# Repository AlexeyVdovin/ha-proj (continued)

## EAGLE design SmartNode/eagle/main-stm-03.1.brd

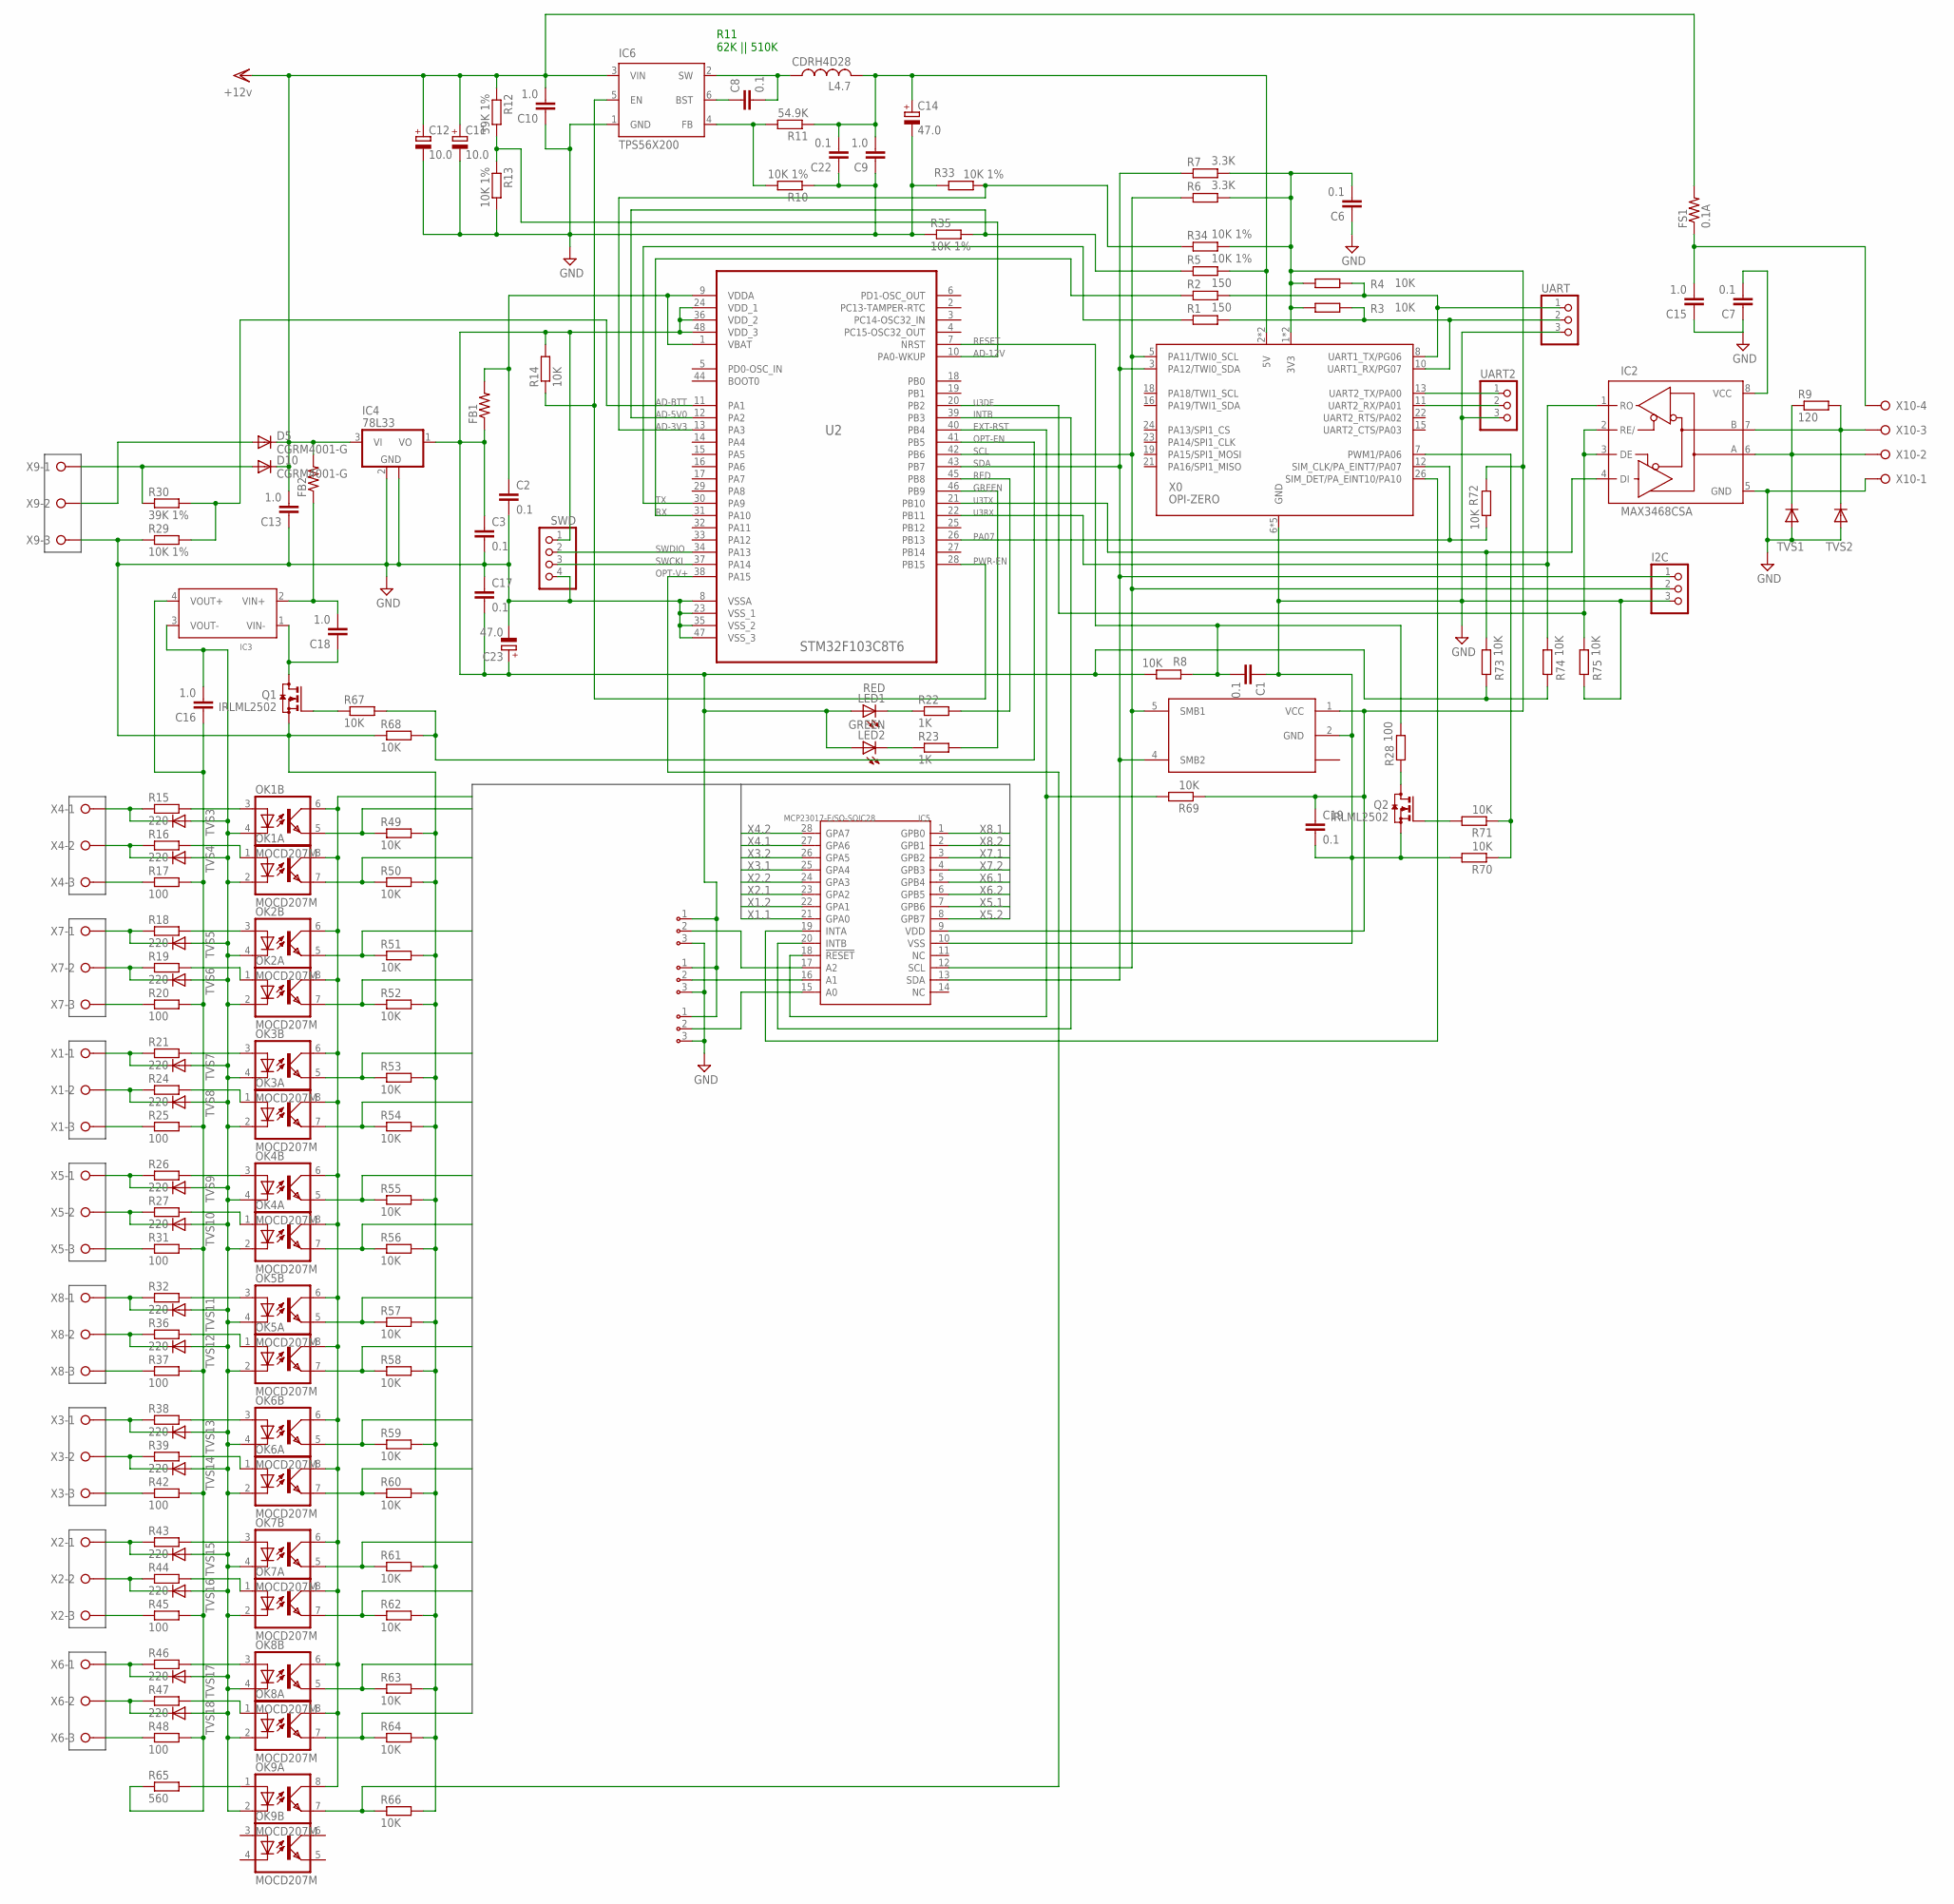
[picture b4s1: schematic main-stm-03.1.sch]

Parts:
A0, A1, A2: ADDR3PIN0603; 0603-3PIN
C1, C2, C3, C17, C19: 0.1; C0603
C6, C7, C8, C22: 0.1; C0805
C9: 1.0; C0805
C10, C13, C15, C16, C18: 1.0; C1206
C11, C12: 10.0; C/6032-28R
C14, C23: 47.0; B/3528-21R
D5, D10: CGRM4001-G; SOD-123_MINI-SMA
FB1: R-US_R0805; R0805
FB2: R-US_R1206; R1206
FS1: 0.1A; R1210
I2C: PINHD-1X3; 1X03
IC2: MAX3468CSA; SO08
IC3: DC-DC-CONV-4PIN-ISOLATINGMURATA-NME-05-12-SERIES; DC-DC-MURATA-NME-05-12-SERIES
IC4: 78L33; SOT89
IC5: MCP23017-E/SO-SOIC28; SOIC28-1.27-17.9X7.5MM
IC6: TPS56X200; TSOT23-6_DDC
IC7: LTC1694; SOT23-5
L4.7: CDRH4D28
LED1: RED; CHIPLED_1206
LED2: GREEN; CHIPLED_1206
OK1, OK2, OK3, OK4, OK5, OK6, OK7, OK8, OK9: MOCD207M; SOIC08-FAIRCHILD
Q1, Q2: IRLML2502; SOT23
R1, R2: 150; R0603
R3, R4, R8, R14, R49, R50, R51, R52, R53, R54, R55, R56, R57, R58, R59, R60, R61, R62, R63, R64, R66, R67, R68, R69, R70, R71, R72, R73, R74, R75: 10K; R0603
R5, R10, R13, R29, R33, R34, R35: 10K 1%; R0603
R6, R7: 3.3K; R0603
R9: 120; R1206
R11: 54.9K; R0603
R12, R30: 39K 1%; R0603
R15, R16, R18, R19, R21, R24, R26, R27, R32, R36, R38, R39, R43, R44, R46, R47: 220; R0603
R17, R20, R25, R28, R31, R37, R42, R45, R48: 100; R0603
R22, R23: 1K; R0603
R65: 560; R0603
SWD: PINHD-1X4; 1X04
TVS1, TVS2, TVS3, TVS4, TVS5, TVS6, TVS7, TVS8, TVS9, TVS10, TVS11, TVS12, TVS13, TVS14, TVS15, TVS16, TVS17, TVS18: DIODE-SOD323-W; SOD323-W
U2: STM32F103C8T6; QFP50P900X900X160-48N
UART, UART2: PINHD-1X3; 1X03
X0: OPI-ZERO; OPI0
X1, X2, X3, X4, X5, X6, X7, X8, X9: W237-03P; W237-133
X10: W237-04P; W237-4P

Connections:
12V: C10.2, C11.+, C12.+, C13.2, D5.C, D10.C, FB2.2, FS1.2, IC4.3 (VI), IC6.3 (VIN), R12.1
AD-3V3: R33.1, R34.1, U2.13 (PA3)
AD-5V0: R5.1, R35.2, U2.12 (PA2)
AD-12V: R12.2, R13.1, U2.10 (PA0-WKUP)
AD-BTT: R29.2, R30.2, U2.11 (PA1)
EXT-RST: IC5.18 (!RESET), R69.2, U2.40 (PB4)
GND: A0.3, A1.3, A2.3, C1.1, C2.2, C3.2, C6.1, C7.1, C9.1, C10.1, C11.-, C12.-, C13.1, C14.-, C15.1, C17.1, C19.2, C22.1, C23.-, I2C.3, IC2.5 (GND), IC4.2 (GND), IC4.2@1 (GND), IC5.10 (VSS), IC6.1 (GND), IC7.2 (GND), Q1.2 (S), Q2.2 (S), R10.1, R13.2, R29.1, R33.2, R35.1, R49.2, R50.2, R51.2, R52.2, R53.2, R54.2, R55.2, R56.2, R57.2, R58.2, R59.2, R60.2, R61.2, R62.2, R63.2, R64.2, R66.2, R68.1, R70.2, R75.1, SWD.4, TVS1.A, TVS2.A, U2.8 (VSSA), U2.23 (VSS_1), U2.35 (VSS_2), U2.47 (VSS_3), UART.3, UART2.3, X0.6 (GND), X0.9 (GND), X0.14 (GND), X0.20 (GND), X0.25 (GND), X9.3, X10.1
GREEN: R23.2, U2.46 (PB9)
INTA: IC5.19 (INTA), X0.26 (SIM_DET/PA_EINT10/PA10)
INTB: IC5.20 (INTB), U2.39 (PB3)
unnamed: C8.2, IC6.2 (SW), L4.7.P$1 (1)
unnamed: Q2.3 (D), R28.1
unnamed: Q2.1 (G), R71.2
unnamed: D5.A, X9.2
unnamed: OK1.3 (A), R15.2
unnamed: C8.1, IC6.6 (BST)
unnamed: IC6.4 (FB), R10.2, R11.2
unnamed: C15.2, FS1.1, X10.4
unnamed: R15.1, TVS3.C, X4.1
unnamed: R16.1, TVS4.C, X4.2
unnamed: R17.1, X4.3
unnamed: D10.A, R30.1, X9.1
unnamed: R18.1, TVS5.C, X7.1
unnamed: R19.1, TVS6.C, X7.2
unnamed: R20.1, X7.3
unnamed: OK2.3 (A), R18.2
unnamed: R21.1, TVS7.C, X1.1
unnamed: OK3.3 (A), R21.2
unnamed: R24.1, TVS8.C, X1.2
unnamed: R25.1, X1.3
unnamed: R26.1, TVS9.C, X5.1
unnamed: R27.1, TVS10.C, X5.2
unnamed: R31.1, X5.3
unnamed: R32.1, TVS11.C, X8.1
unnamed: R36.1, TVS12.C, X8.2
unnamed: R37.1, X8.3
unnamed: R38.1, TVS13.C, X3.1
unnamed: R39.1, TVS14.C, X3.2
unnamed: R42.1, X3.3
unnamed: R43.1, TVS15.C, X2.1
unnamed: R44.1, TVS16.C, X2.2
unnamed: R45.1, X2.3
unnamed: R46.1, TVS17.C, X6.1
unnamed: R47.1, TVS18.C, X6.2
unnamed: R48.1, X6.3
unnamed: OK4.3 (A), R26.2
unnamed: OK5.3 (A), R32.2
unnamed: OK6.3 (A), R38.2
unnamed: OK7.3 (A), R43.2
unnamed: OK8.3 (A), R46.2
unnamed: C16.1, IC3.4 (VOUT+), R17.2, R20.2, R25.2, R31.2, R37.2, R42.2, R45.2, R48.2, R65.1
unnamed: OK1.1 (A), R16.2
unnamed: OK2.1 (A), R19.2
unnamed: OK3.1 (A), R24.2
unnamed: OK4.1 (A), R27.2
unnamed: OK5.1 (A), R36.2
unnamed: OK6.1 (A), R39.2
unnamed: OK7.1 (A), R44.2
unnamed: OK8.1 (A), R47.2
unnamed: C16.2, IC3.3 (VOUT-), OK1.2 (C), OK1.4 (C), OK2.2 (C), OK2.4 (C), OK3.2 (C), OK3.4 (C), OK4.2 (C), OK4.4 (C), OK5.2 (C), OK5.4 (C), OK6.2 (C), OK6.4 (C), OK7.2 (C), OK7.4 (C), OK8.2 (C), OK8.4 (C), OK9.2 (C), TVS3.A, TVS4.A, TVS5.A, TVS6.A, TVS7.A, TVS8.A, TVS9.A, TVS10.A, TVS11.A, TVS12.A, TVS13.A, TVS14.A, TVS15.A, TVS16.A, TVS17.A, TVS18.A
unnamed: LED1.C, R22.1
unnamed: OK9.1 (A), R65.2
unnamed: Q1.1 (G), R67.1
unnamed: C18.1, IC3.1 (VIN-), Q1.3 (D)
unnamed: C18.2, FB2.1, IC3.2 (VIN+)
unnamed: A0.2, IC5.15 (A0)
unnamed: A1.2, IC5.16 (A1)
unnamed: A2.2, IC5.17 (A2)
unnamed: LED2.C, R23.1
OPT-EN: R67.2, R68.2, U2.41 (PB5)
OPT-V+: OK9.7 (EMIT), R66.1, U2.38 (PA15)
PA06: R70.1, R71.1, X0.7 (PWM1/PA06)
PA07: R72.2, U2.26 (PB13), X0.12 (SIM_CLK/PA_EINT7/PA07)
PWR-EN: IC6.5 (EN), R14.1, U2.28 (PB15)
RED: R22.2, U2.45 (PB8)
RESET: C1.2, R8.1, R28.2, U2.7 (NRST)
RS485-A: IC2.6 (A), R9.1, TVS1.C, X10.2
RS485-B: IC2.7 (B), R9.2, TVS2.C, X10.3
RX: R2.1, U2.31 (PA10)
SCL: I2C.2, IC5.12 (SCL), IC7.5 (SMB1), R6.1, U2.42 (PB6), X0.5 (PA11/TWI0_SCL)
SDA: I2C.1, IC5.13 (SDA), IC7.4 (SMB2), R7.1, U2.43 (PB7), X0.3 (PA12/TWI0_SDA)
SWCKL: SWD.3, U2.37 (PA14)
SWDIO: SWD.2, U2.34 (PA13)
TX: R1.1, U2.30 (PA9)
U3DE: IC2.2 (RE/), IC2.3 (DE), R75.2, U2.20 (PB2)
U3RX: IC2.1 (RO), R74.2, U2.22 (PB11)
U3TX: IC2.4 (DI), R73.2, U2.21 (PB10)
VCC: A0.1, A1.1, A2.1, C3.1, C7.2, C17.2, C23.+, FB1.1, IC2.8 (VCC), IC4.1 (VO), LED1.A, LED2.A, R8.2, R14.2, R73.1, R74.1, SWD.1, U2.24 (VDD_1), U2.36 (VDD_2), U2.48 (VDD_3)
VDDA: C2.1, FB1.2, U2.1 (VBAT), U2.9 (VDDA)
X1.1: IC5.21 (GPA0), OK3.5 (EMIT), R53.1
X1.2: IC5.22 (GPA1), OK3.7 (EMIT), R54.1
X2.1: IC5.23 (GPA2), OK7.5 (EMIT), R61.1
X2.2: IC5.24 (GPA3), OK7.7 (EMIT), R62.1
X3.1: IC5.25 (GPA4), OK6.5 (EMIT), R59.1
X3.2: IC5.26 (GPA5), OK6.7 (EMIT), R60.1
X4.1: IC5.27 (GPA6), OK1.5 (EMIT), R49.1
X4.2: IC5.28 (GPA7), OK1.7 (EMIT), R50.1
X5.1: IC5.7 (GPB6), OK4.5 (EMIT), R55.1
X5.2: IC5.8 (GPB7), OK4.7 (EMIT), R56.1
X6.1: IC5.5 (GPB4), OK8.5 (EMIT), R63.1
X6.2: IC5.6 (GPB5), OK8.7 (EMIT), R64.1
X7.1: IC5.3 (GPB2), OK2.5 (EMIT), R51.1
X7.2: IC5.4 (GPB3), OK2.7 (EMIT), R52.1
X8.1: IC5.1 (GPB0), OK5.5 (EMIT), R57.1
X8.2: IC5.2 (GPB1), OK5.7 (EMIT), R58.1
Z2RX: UART2.2, X0.11 (UART2_RX/PA01)
Z2TX: UART2.1, X0.13 (UART2_TX/PA00)
Z3V3: C6.2, C19.1, IC5.9 (VDD), IC7.1 (VCC), OK1.6 (COL), OK1.8 (COL), OK2.6 (COL), OK2.8 (COL), OK3.6 (COL), OK3.8 (COL), OK4.6 (COL), OK4.8 (COL), OK5.6 (COL), OK5.8 (COL), OK6.6 (COL), OK6.8 (COL), OK7.6 (COL), OK7.8 (COL), OK8.6 (COL), OK8.8 (COL), OK9.8 (COL), R3.1, R4.1, R6.2, R7.2, R34.2, R69.1, R72.1, X0.1 (3V3), X0.17 (3V3)
Z5V: C9.2, C14.+, C22.2, L4.7.P$2 (2), R5.2, R11.1, X0.2 (5V), X0.4 (5V)
ZRX: R1.2, R3.2, UART.2, X0.10 (UART1_RX/PG07)
ZTX: R2.2, R4.2, UART.1, X0.8 (UART1_TX/PG06)

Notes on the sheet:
R11 62K || 510K

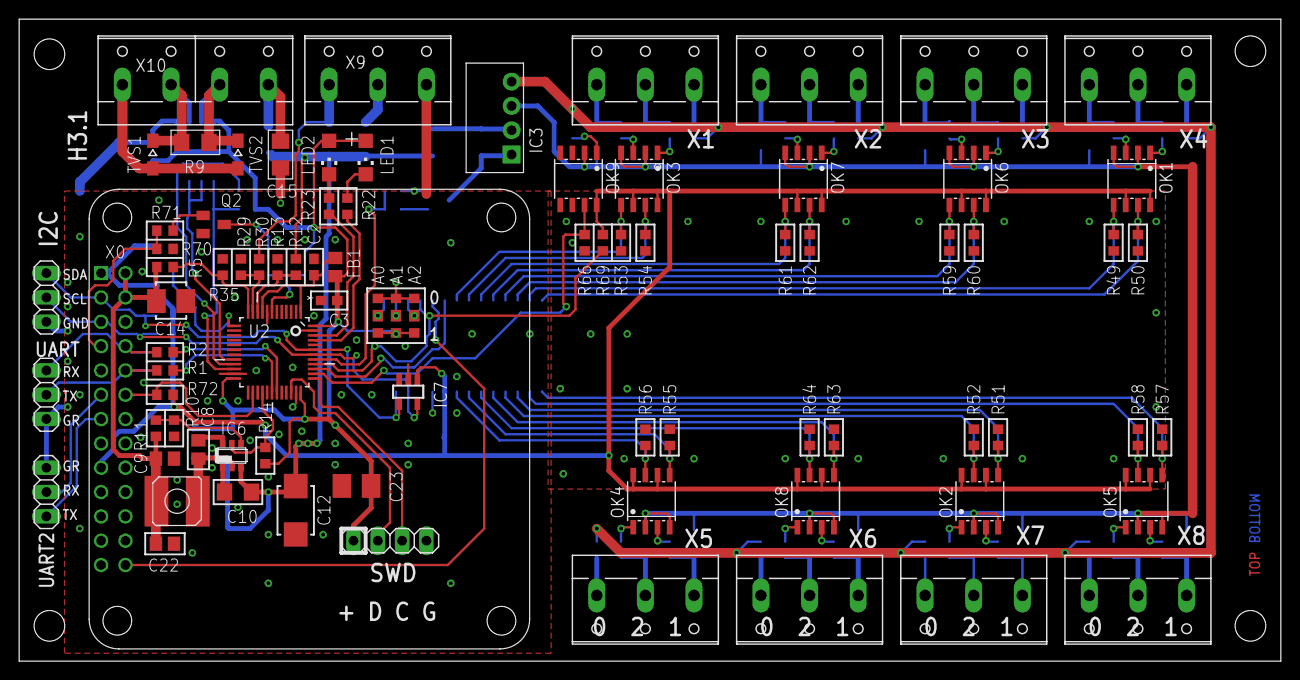
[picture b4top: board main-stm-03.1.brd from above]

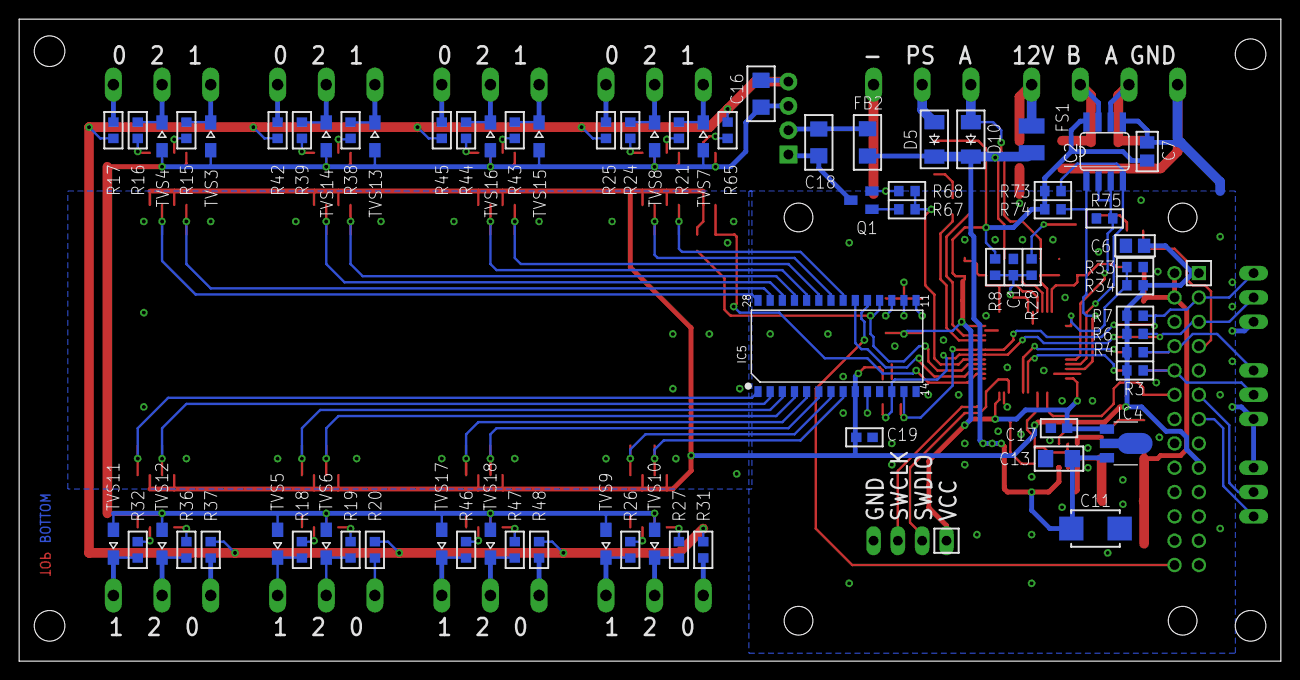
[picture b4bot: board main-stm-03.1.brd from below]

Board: 2 copper layers, 131.8 x 67.0 mm, 154 parts (71 on the bottom side), 111 nets.

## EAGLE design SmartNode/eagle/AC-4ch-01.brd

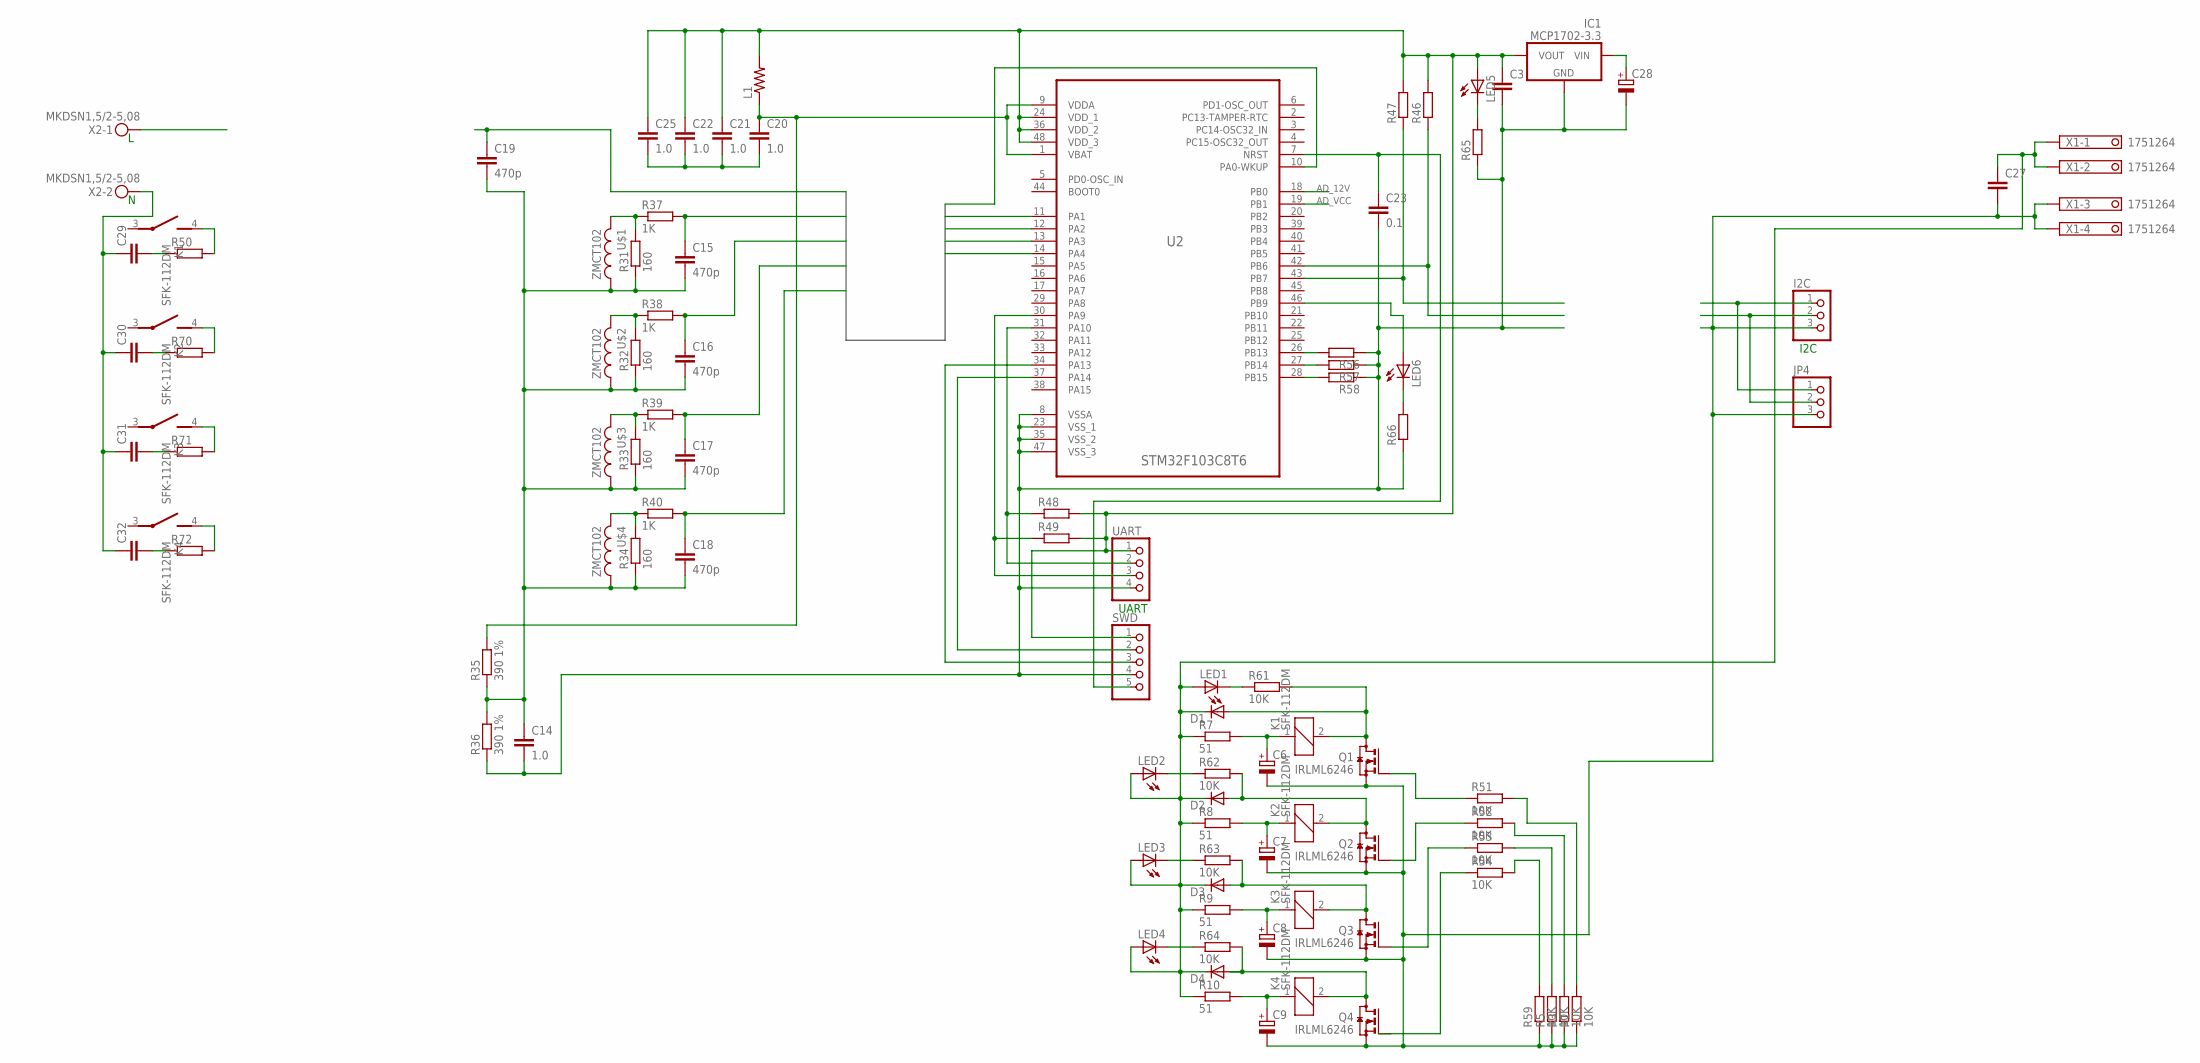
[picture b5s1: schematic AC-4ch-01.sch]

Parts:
C3: C-EUC0805; C0805
C6, C7, C8, C9: CPOL-EUE3.5-8; E3,5-8
C14, C20, C21, C22, C25: 1.0; C0805
C15, C16, C17, C18, C19: 470p; C0603
C23: 0.1; C0603
C27: C-EUC1206; C1206
C28: CPOL-EUSMCB; SMC_B
C29, C30, C31, C32: C-EU225-087X268; C225-087X268
D1, D2, D3, D4: DIODE-SOD123; SOD123
I2C: PINHD-1X3; 1X03
IC1: MCP1702-3.3; SOT23-3-ROTATED
JP4: PINHD-1X3; 1X03
K1, K2, K3, K4: SFK-112DM; SFK112
L1: R-US_M0805; M0805
LED1, LED2, LED3, LED4, LED5, LED6: LEDCHIP-LED0805; CHIP-LED0805
Q1, Q2, Q3, Q4: IRLML6246; SOT23
R1, R3, R5, R51, R52, R53, R54, R59, R61, R62, R63, R64: 10K; R0603
R7, R8, R9, R10: 51; R1206
R31, R32, R33, R34: 160; R0603
R35, R36: 390 1%; R0603
R37, R38, R39, R40: 1K; R0603
R46, R47, R48, R49, R56, R57, R58, R65, R66: R-EU_R0603; R0603
R50, R70, R71, R72: R-EU_0414/5V; 0414V
SWD: PINHD-1X5; 1X05
U2: STM32F103C8T6; QFP50P900X900X160-48N
U$1, U$2, U$3, U$4: ZMCT102; ZMCT
UART: PINHD-1X4; 1X04
X1: 1751264
X2: MKDSN1,5/2-5,08

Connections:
0V: C3.2, C14.2, C20.2, C21.2, C22.2, C23.2, C25.2, C28.-, IC1.1 (GND), R36.1, R56.1, R57.1, R58.1, R65.1, R66.1, SWD.4, U2.8 (VSSA), U2.23 (VSS_1), U2.35 (VSS_2), U2.47 (VSS_3), UART.4
3.3V: C3.1, C21.1, C22.1, C25.1, IC1.2 (VOUT), L1.2, LED5.A, R46.2, R47.2, R48.2, R49.2, SWD.1, U2.24 (VDD_1), U2.36 (VDD_2), U2.48 (VDD_3), UART.1
+12V: C27.1, D1.C, D2.C, D3.C, D4.C, LED1.A, LED2.A, LED3.A, LED4.A, R7.1, R8.1, R9.1, R10.1, X1.1, X1.2
A0: C18.1, R40.2, U2.10 (PA0-WKUP)
A1: C17.1, R39.2, U2.11 (PA1)
A2: C16.1, R38.2, U2.12 (PA2)
A3: C15.1, R37.2, U2.13 (PA3)
A4: C19.1, U2.14 (PA4)
A9: C14.1, C15.2, C16.2, C17.2, C18.2, C19.2, R31.1, R32.1, R33.1, R34.1, R35.1, R36.2, U$1.1, U$2.1, U$3.1, U$4.1
AD_12V: U2.18 (PB0)
AD_VCC: U2.19 (PB1)
GND: C6.-, C7.-, C8.-, C9.-, C27.2, I2C.3, JP4.3, Q1.2 (S), Q2.2 (S), Q3.2 (S), Q4.2 (S), R1.1, R3.1, R5.1, R59.1, X1.3, X1.4
I2C: I2C.2, JP4.2
unnamed: C29.1, C30.1, C31.1, C32.1, X2.2
unnamed: C29.2, R50.1
unnamed: R31.2, R37.1, U$1.2
unnamed: R32.2, R38.1, U$2.2
unnamed: R56.2, U2.26 (PB13)
unnamed: C30.2, R70.1
unnamed: C31.2, R71.1
unnamed: LED1.C, R61.1
unnamed: R47.1, U2.43 (PB7)
unnamed: R33.2, R39.1, U$3.2
unnamed: R46.1, U2.42 (PB6)
unnamed: R34.2, R40.1, U$4.2
unnamed: LED2.C, R62.1
unnamed: C32.2, R72.1
unnamed: LED3.C, R63.1
unnamed: LED4.C, R64.1
unnamed: LED5.C, R65.2
unnamed: LED6.C, R66.2
unnamed: LED6.A, U2.46 (PB9)
unnamed: R57.2, U2.27 (PB14)
unnamed: R5.2, R53.2
unnamed: C23.1, SWD.5, U2.7 (NRST)
unnamed: R3.2, R52.2
unnamed: R1.2, R51.2
unnamed: R54.2, R59.2
unnamed: R58.2, U2.28 (PB15)
unnamed: Q1.1 (G), R51.1
unnamed: Q2.1 (G), R52.1
unnamed: Q3.1 (G), R53.1
unnamed: Q4.1 (G), R54.1
unnamed: C28.+, IC1.3 (VIN)
unnamed: D2.A, K2.2, Q2.3 (D), R62.2
unnamed: C7.+, K2.1, R8.2
unnamed: C8.+, K3.1, R9.2
unnamed: D3.A, K3.2, Q3.3 (D), R63.2
unnamed: C9.+, K4.1, R10.2
unnamed: D4.A, K4.2, Q4.3 (D), R64.2
unnamed: D1.A, K1.2, Q1.3 (D), R61.2
unnamed: C6.+, K1.1, R7.2
unnamed: K1.4 (S), R50.2
unnamed: K2.4 (S), R70.2
unnamed: K3.4 (S), R71.2
unnamed: K4.4 (S), R72.2
unnamed: C20.1, L1.1, R35.2, U2.1 (VBAT), U2.9 (VDDA)
RX: R48.1, U2.31 (PA10), UART.2
SDA: I2C.1, JP4.1
SWCLK: SWD.2, U2.37 (PA14)
SWDIO: SWD.3, U2.34 (PA13)
TX: R49.1, U2.30 (PA9), UART.3

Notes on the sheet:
UART
I2C

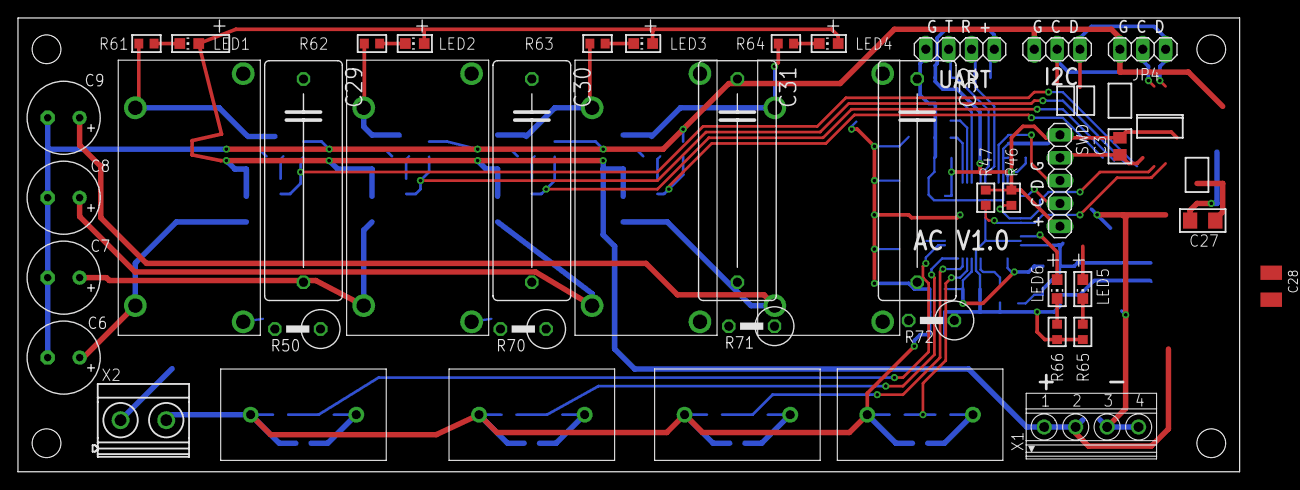
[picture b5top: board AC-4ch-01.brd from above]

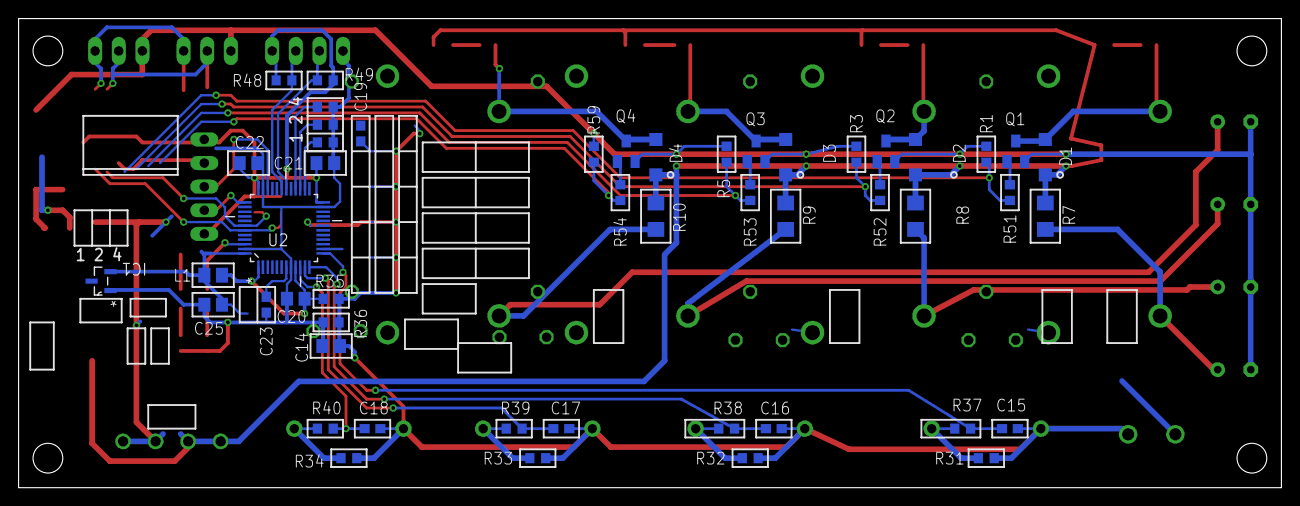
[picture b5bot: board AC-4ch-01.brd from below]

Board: 2 copper layers, 135.9 x 50.5 mm, 92 parts (49 on the bottom side), 60 nets.

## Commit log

2014-08-13 SensorNode: Initial commit
2014-08-14 Move common files to library
2014-08-14 rsGate: Initial rs485 implementation
2014-08-14 rsGate: Initial gateway implementation
2014-08-14 rsGate: Bugfix
2014-08-19 rsGate: Improve rs485 handling
2014-08-19 SensorNode: AVR cross-compile
2014-08-19 rsLib: AVR cross-compile
2014-08-20 Makefile updated for better cross-compile handling
2014-08-20 SensorNode: Simple ping functionality
2014-08-21 rsGate: Add packets queue
2014-08-21 rsGate: Response timeout
2014-08-22 Compilation fixes
2014-08-25 rsLib: 1Wire library
2014-08-25 rsLib: ADC implementation
2014-08-25 SensorNode: IO initialization
2014-08-26 rsLib: Fix packet structure
2014-08-26 Fix rsGate to match new packet structure
2014-08-26 rsLib: add power management to long delays
2014-08-26 SensorNode: Fix timer interrupts + comm debugging
2014-08-26 rsLib: Re-factor packet implementation
2014-08-26 rsGate: Update according to new packet API
2014-08-26 rsLib: Registration procedure description
2014-08-28 rsLib: Registration procedure clarified
2014-08-28 rsLib: ds1820 added to the Lib
2014-08-28 rsLib: Improve packet framing handling
2014-08-31 rsLib: Improve ADC handling
2014-08-31 SensorNode: Implement ds1820 processing + command processing stub
2014-09-01 SensorNode: EEPROM config added
2014-09-01 SensorNode: initial implementation for '02 - read sensor' command
2014-09-02 rsLib: PWM module added
2014-09-02 SensorNode: Read sensors
2014-09-03 SensorNode: Initial implementation for '04 - set actuator' command
2014-09-03 rsLib: Added ds1820 sensor count
2014-09-03 SensorNode: Implemented ds1820 rescan command
2014-09-03 SensorNode: read command processing fix
2014-09-04 SensorNode: Make ds1820 read more reliable
2014-09-05 rsLib: Fix ADC mode
2014-09-05 rsLib: Extend PWM functionality + fix SensorNode
2014-09-21 rsLib: Add LED display driver
2014-09-22 ControlNode: Stub implementation + build redesign
2014-09-22 SensorNode: build redesign
2014-09-22 rsGate: build redesign
2014-09-24 rsLib: SW PWM module added
2014-09-24 ControlNode: SW PWM used + cosmetics
2014-09-30 SensorNode: Makefile fix + cosmetic changes
2014-09-30 rsLib/timer: fix timer overflow
2014-10-01 rsLib: Add non-GNU time.h support
2014-10-02 Redisign: io_init moved to main.c due to difference in MCU registers
2014-10-03 SensorNode: Restore Timer functionality + PWM init moved to main.c
2014-10-06 rsLib/ds1820: Add custom pin support
2014-10-06 ControlNode: Initial functionality
2015-01-26 Start bootloader development
2015-01-26 Initial implementation
2015-01-28 Initial host side bootloader support
2015-02-02 Debug code
2015-02-04 Initial bootloader test passed
2015-03-04 bootloader fixes
2015-03-09 Switch to 328p
2015-03-15 Migrating wiki contents from Google Code
2015-03-17 Node registration initial implementation
2018-08-28 Greenhouse Node initial commit
2018-09-02 TWI slave initial commit
2018-09-04 flash script
2018-09-04 first launch
2018-09-07 Working i2c slave IO
2018-09-07 printf redirected to uart and timer fix
2018-09-09 ADC calibration
2018-09-09 Power monitoring
2018-09-10 Host i2c functions
2018-09-15 Initial DS2482 support
2018-09-15 Initial DS18B20 support
2018-09-15 Reading DS18B20 temperature
2018-11-07 Delayed shutdown added
2018-12-15 Reading m328 i2c registers
2018-12-15 m328 debug
2018-12-15 Select i2c slave address for ds2482
2019-03-05 Fix 1W-Search and m328 bugs
2019-03-07 Relay control on m328
2019-03-07 Write to m328 regs
2019-03-07 Fix ambiguous ‘else’
2019-03-09 Fix m328 relay control
2019-03-09 Memcached php stub
2019-03-09 Save T readings in memchached
2019-03-10 Main temperature proc
2019-03-10 Sensors map
2019-03-10 Fix for temperature processing
2019-03-10 Code makeup
2019-03-10 Full control loop
2019-03-10 Web UI stub
2019-03-10 Web page with T info
2019-03-10 Control loop redesign
2019-03-10 Min/Max reset scripts
2019-03-10 Fix Min/Max reset scripts
2019-03-10 Fix control loop
2019-03-10 Add default values
2019-03-10 Fix php script execution
2019-03-12 Web control initial implementation
2019-03-13 Fix remote control
2019-03-13 Do not cache status page
2019-03-13 Fix relay status reporting
2019-03-13 Turn OFF all realays in case of power loss
2019-03-14 Time limit for curl.
2019-03-14 Sensor mapping
2019-03-14 Fix avg calculation
2019-03-14 Fix Overload detection
2019-03-14 Handle Pi Zero shutdown condition
2019-03-14 Fix Pi Zero shutdown in power loss case
2019-03-14 Fix misspring
2019-03-14 Monitor Internet connection
2019-03-14 Disable i2c and uart if OPiZ in Power OFF state
2019-03-14 Disable UART and TWI stub
2019-03-29 Apply T correction to sensors
2019-05-14 Use T correction in automation calculations
2019-05-14 Fix i2c stuck in case of Master reset
2019-05-14 Fix compilation warnings
2019-10-09 SmartNode carrier board added
2019-10-09 GH: local changes
2019-10-10 Ann component values to schematic
2019-10-10 Add component values to schematic
2020-02-04 OpiZ changes
2020-02-18 Local debug changes
2020-02-25 Fix i2c bug
2020-03-17 Uptime monitoring
2020-06-02 Reboot in case of 1Wire failure
2020-06-02 Add charts
2020-06-04 Draft file structure
2020-06-04 mqtt-c added
2020-06-05 Single thread event handling
2020-06-05 Contact bounce suppression
2020-06-06 mcp23017 event processing
2020-06-07 mqtt notify
2020-06-07 Telemetry sent to uplink
2020-06-24 Add lights control
2020-11-22 SmartNode: Eagle files + loacal minIni
2020-12-17 Fix MQTT reconnect
2021-03-26 Updated design files
2021-03-26 rs485 io tool
2021-04-01 Basic RX/TX works
2021-04-04 485io slave READ commands
2021-04-04 Fix sleep timeout
2021-04-04 485io read/write basic functionality
2021-11-28 1W enum and read
2021-11-29 Boiler + ds2482 support added
2021-11-29 boiler: Timer interrupts
2021-11-29 VScode settings
2021-11-29 boiler: 1W temperature reading
2021-11-29 boiler: 1W sensors config enum
2021-11-29 boiler: PID control and Water heating
2021-12-20 HA: Device auto registration
2021-12-20 HA: Status reporting
2021-12-26 HA: heating controller integration
2022-02-06 Fixes and improvements. moved to basement
2022-02-19 Fix PID implementation, Improve restore status
2022-04-26 Tune Heating floor PID controller
2022-06-03 final version of hot water and floor control
2022-09-06 Update correct signal names
2022-09-18 2.2 floor HA integration
2022-09-18 more PCB designs
2022-09-18 Configurable entity names
2022-09-18 All config files for: 2.1, 2.2 and boiler
2022-11-02 Fix mqtt stuck in disconneted state
2023-01-09 Rewrite for new stm32 design
2023-01-09 initial compilation
2023-01-11 temperature sensors and business logic
2023-01-13 Watering business logic
2023-01-14 Web is functional. Many bugs fixed on host
2023-01-14 Cosmetic changes
2023-01-17 curl uplink added
2023-03-04 Minimized traffic
2023-03-08 Fix initial control state after reboot
2023-03-11 Fix startup issue
2023-03-18 Set correct sensors and relays
2023-04-10 Add min/max reset by cron
2024-02-04 Fix uplink timeout
2024-03-16 Do not update last watering time on manual run
2024-03-16 Update watering time on set period or duration
2024-03-16 Fix watering time
